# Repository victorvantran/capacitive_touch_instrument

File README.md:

# capacitive_touch_instrument
Capacitive touch instrument built with AT42QT1110 daisy-chained

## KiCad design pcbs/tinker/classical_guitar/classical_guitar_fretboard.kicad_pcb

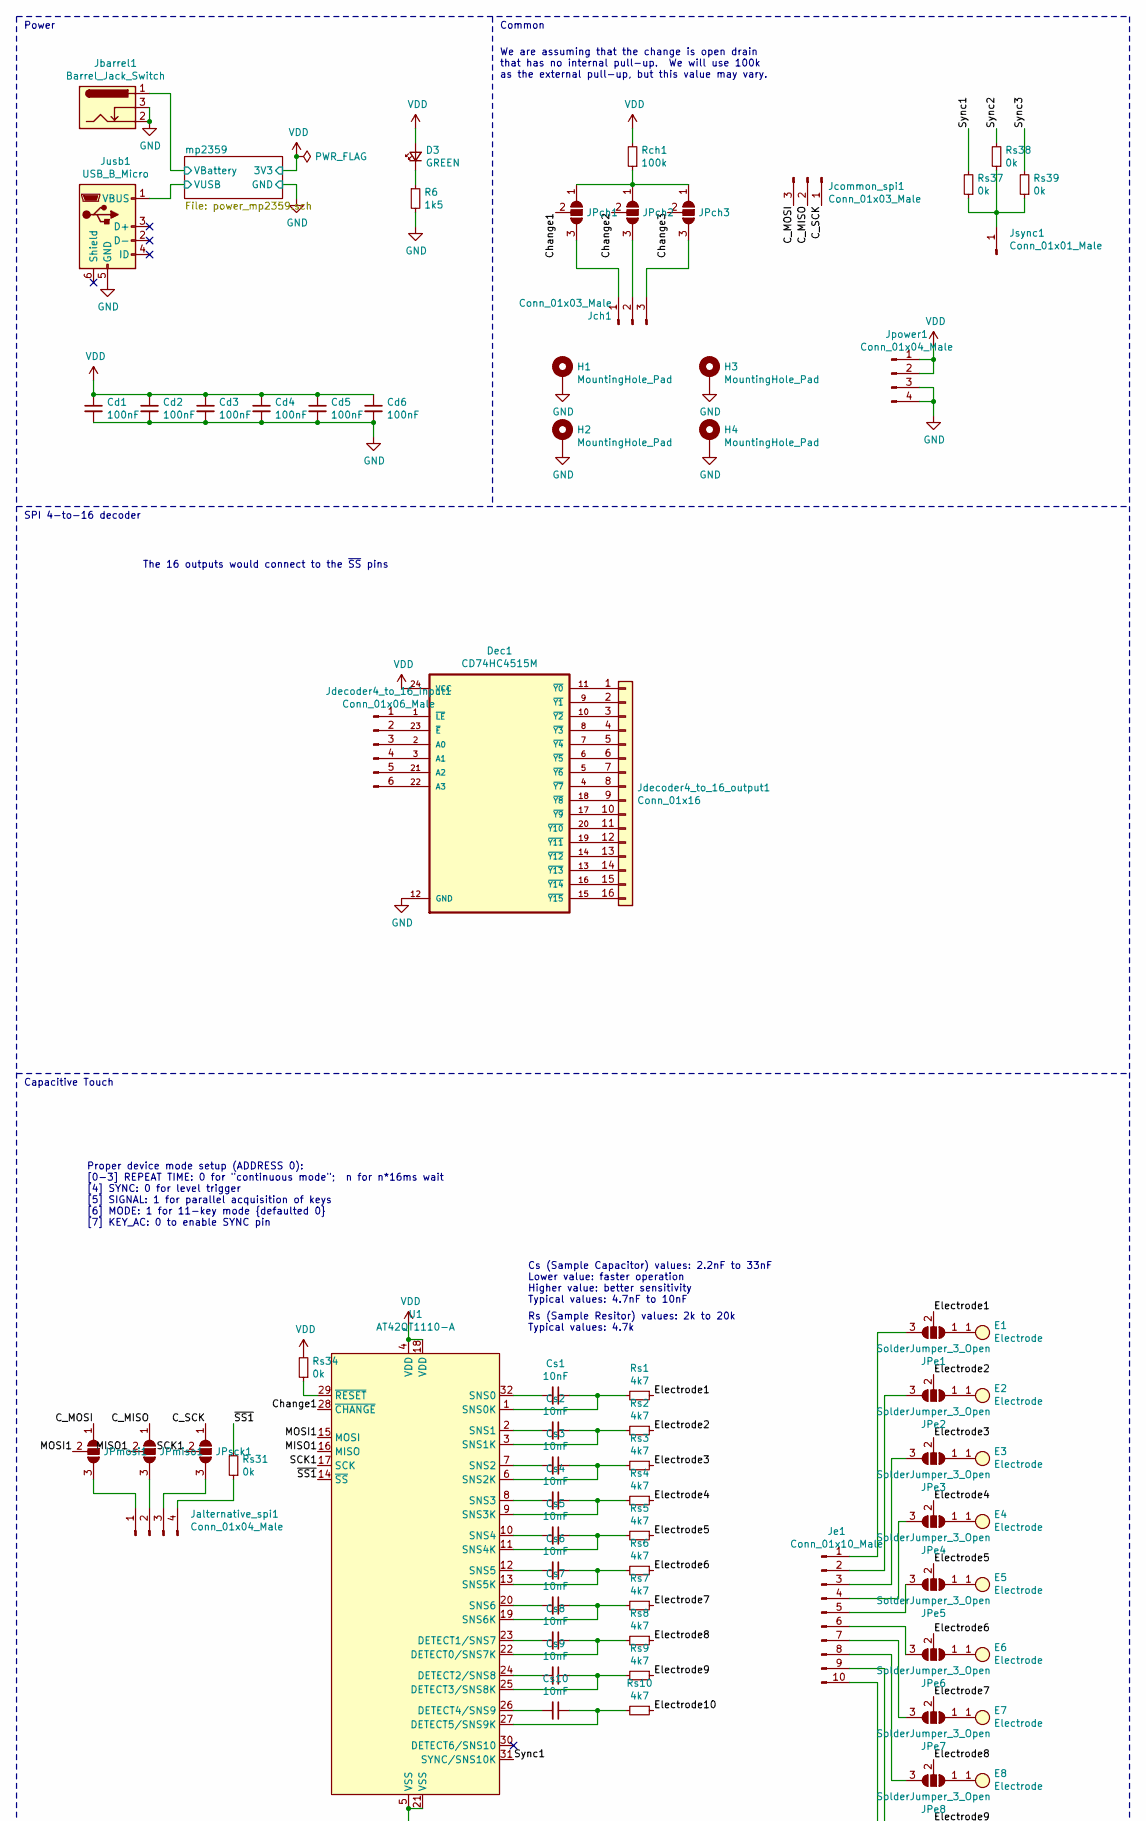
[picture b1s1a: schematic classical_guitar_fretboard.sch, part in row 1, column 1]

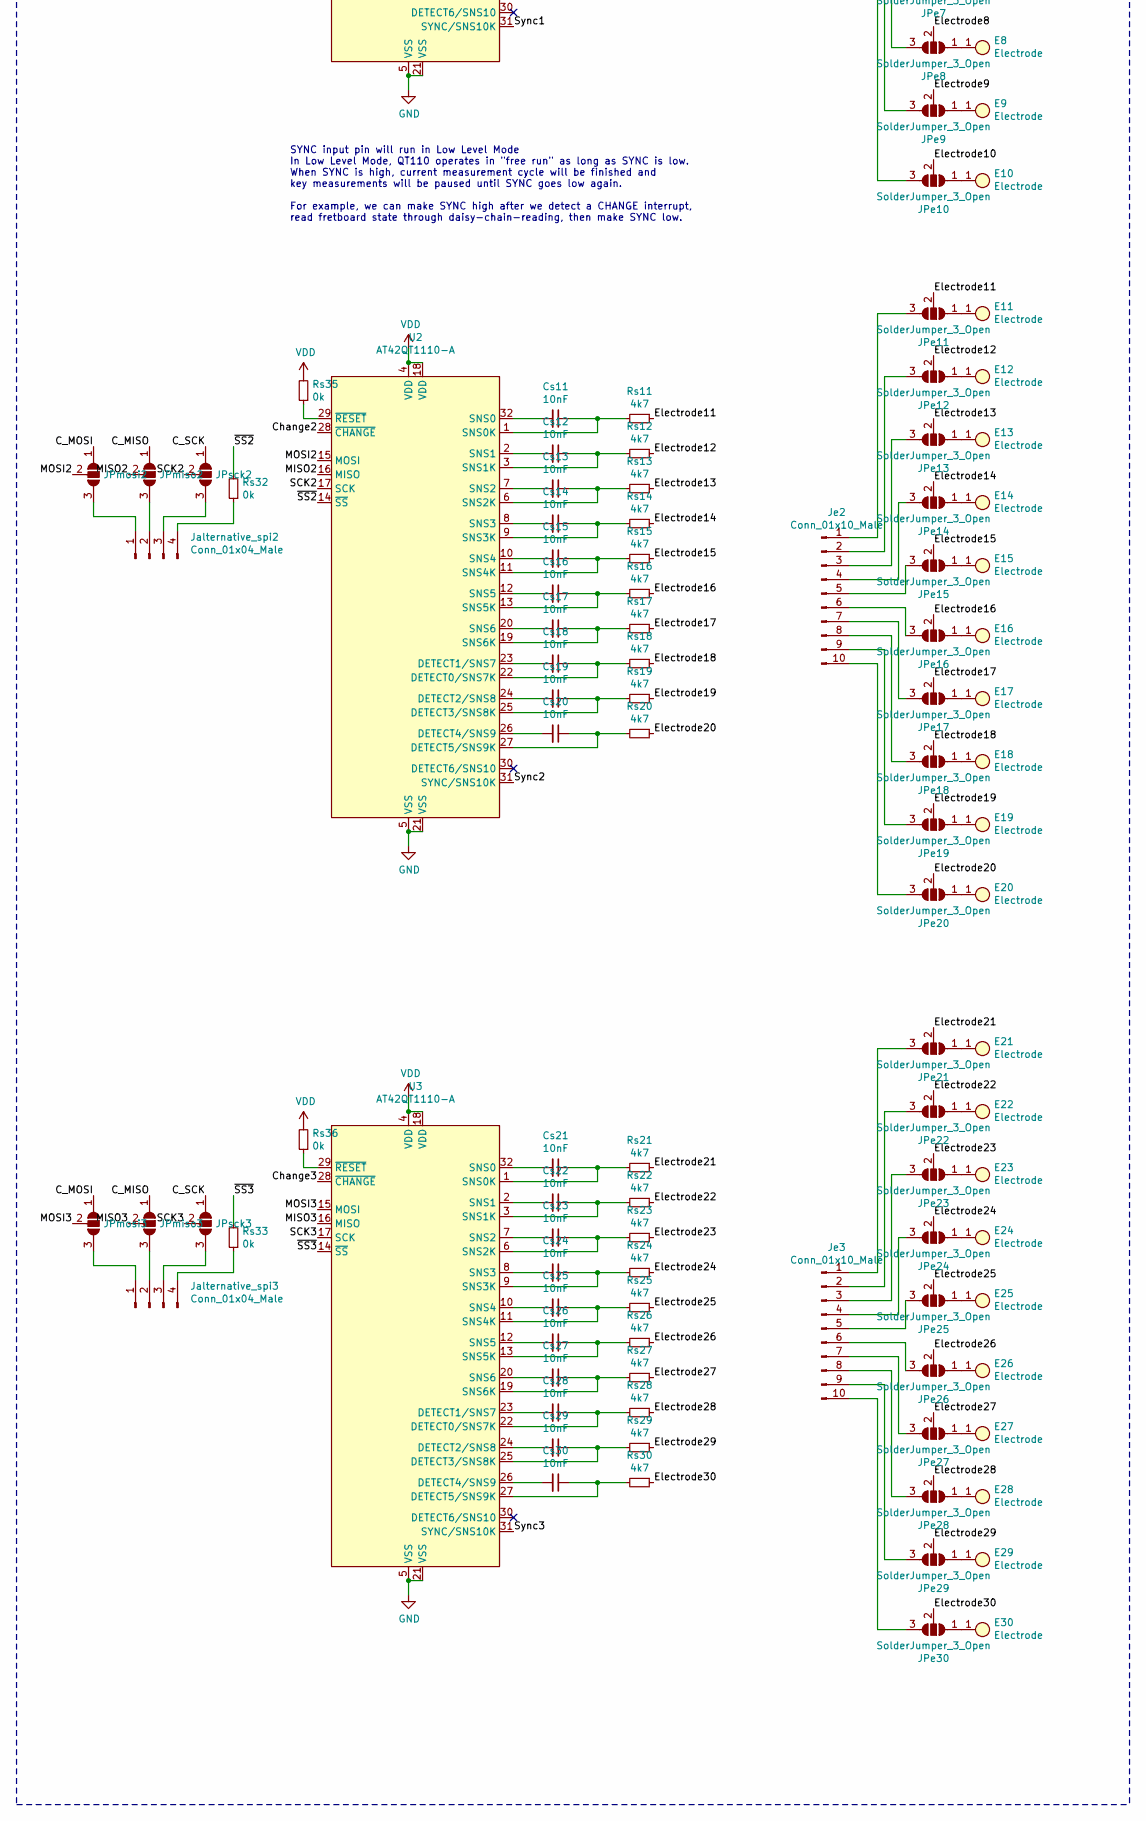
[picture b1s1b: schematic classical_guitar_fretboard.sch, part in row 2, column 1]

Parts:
Cd1, Cd2, Cd3, Cd4, Cd5, Cd6: 100nF; C_0402_1005Metric_Pad0.74x0.62mm_HandSolder
Cs1, Cs2, Cs3, Cs4, Cs5, Cs6, Cs7, Cs8, Cs9, Cs10, Cs11, Cs12, Cs13, Cs14, Cs15, Cs16, Cs17, Cs18, Cs19, Cs20, Cs21, Cs22, Cs23, Cs24, Cs25, Cs26, Cs27, Cs28, Cs29, Cs30: 10nF; C_0603_1608Metric_Pad1.08x0.95mm_HandSolder
D3: GREEN; LED_0603_1608Metric; LCSC Part # C2286
Dec1: CD74HC4515M; SOIC-24W_7.5x15.4mm_P1.27mm
E1, E2, E3, E4, E5, E6, E7, E8, E9, E10, E11, E12, E13, E14, E15, E16, E17, E18, E19, E20, E21, E22, E23, E24, E25, E26, E27, E28, E29, E30: Electrode; Circle_10mm
H1, H2, H3, H4: MountingHole_Pad; MountingHole_4.3mm_M4_Pad_Via
JPch1, JPch2, JPch3: SolderJumper_3_Open; SolderJumper-3_P1.3mm_Open_RoundedPad1.0x1.5mm_NumberLabels
JPe1, JPe2, JPe3, JPe4, JPe5, JPe6, JPe7, JPe8, JPe9, JPe10, JPe11, JPe12, JPe13, JPe14, JPe15, JPe16, JPe17, JPe18, JPe19, JPe20, JPe21, JPe22, JPe23, JPe24, JPe25, JPe26, JPe27, JPe28, JPe29, JPe30: SolderJumper_3_Open; SolderJumper-3_P1.3mm_Open_RoundedPad1.0x1.5mm_NumberLabels
JPmiso1, JPmiso2, JPmiso3: SolderJumper_3_Open; SolderJumper-3_P1.3mm_Open_RoundedPad1.0x1.5mm_NumberLabels
JPmosi1, JPmosi2, JPmosi3: SolderJumper_3_Open; SolderJumper-3_P1.3mm_Open_RoundedPad1.0x1.5mm_NumberLabels
JPsck1, JPsck2, JPsck3: SolderJumper_3_Open; SolderJumper-3_P1.3mm_Open_RoundedPad1.0x1.5mm_NumberLabels
Jalternative_spi1, Jalternative_spi2, Jalternative_spi3: Conn_01x04_Male; PinSocket_1x04_P2.54mm_Vertical
Jbarrel1: Barrel_Jack_Switch; BarrelJack_Horizontal
Jch1: Conn_01x03_Male; PinSocket_1x03_P2.54mm_Vertical
Jcommon_spi1: Conn_01x03_Male; PinSocket_1x03_P2.54mm_Vertical
Jdecoder4_to_16_input1: Conn_01x06_Male; PinHeader_1x06_P2.54mm_Vertical
Jdecoder4_to_16_output1: Conn_01x16; PinSocket_1x16_P2.54mm_Vertical
Je1, Je2, Je3: Conn_01x10_Male; PinSocket_1x10_P2.54mm_Vertical
Jpower1: Conn_01x04_Male; PinSocket_1x04_P2.54mm_Vertical
Jsync1: Conn_01x01_Male; PinSocket_1x01_P2.54mm_Vertical
Jusb1: USB_B_Micro; USB_Micro-B_Amphenol_10118194_Horizontal
R6: 1k5; R_0603_1608Metric; LCSC Part # C22843
Rch1: 100k; R_0603_1608Metric_Pad0.98x0.95mm_HandSolder
Rs1, Rs2, Rs3, Rs4, Rs5, Rs6, Rs7, Rs8, Rs9, Rs10, Rs11, Rs12, Rs13, Rs14, Rs15, Rs16, Rs17, Rs18, Rs19, Rs20, Rs21, Rs22, Rs23, Rs24, Rs25, Rs26, Rs27, Rs28, Rs29, Rs30: 4k7; R_0603_1608Metric_Pad0.98x0.95mm_HandSolder
Rs31, Rs32, Rs33, Rs34, Rs35, Rs36, Rs37, Rs38, Rs39: 0k; R_0603_1608Metric_Pad0.98x0.95mm_HandSolder
U1, U2, U3: AT42QT1110-A; TQFP-32_7x7mm_P0.8mm

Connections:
/C_MISO: JPmiso1.1 (A), JPmiso2.1 (A), JPmiso3.1 (A), Jcommon_spi1.2
/C_MOSI: JPmosi1.1 (A), JPmosi2.1 (A), JPmosi3.1 (A), Jcommon_spi1.3
/C_SCK: JPsck1.1 (A), JPsck2.1 (A), JPsck3.1 (A), Jcommon_spi1.1
/Change1: JPch1.2 (C), U1.28 (~CHANGE)
/Change2: JPch2.2 (C), U2.28 (~CHANGE)
/Change3: JPch3.2 (C), U3.28 (~CHANGE)
/Electrode1: JPe1.2 (C), Rs1.1
/Electrode2: JPe2.2 (C), Rs2.1
/Electrode3: JPe3.2 (C), Rs3.1
/Electrode4: JPe4.2 (C), Rs4.1
/Electrode5: JPe5.2 (C), Rs5.1
/Electrode6: JPe6.2 (C), Rs6.1
/Electrode7: JPe7.2 (C), Rs7.1
/Electrode8: JPe8.2 (C), Rs8.1
/Electrode9: JPe9.2 (C), Rs9.1
/Electrode10: JPe10.2 (C), Rs10.1
/Electrode11: JPe11.2 (C), Rs11.1
/Electrode12: JPe12.2 (C), Rs12.1
/Electrode13: JPe13.2 (C), Rs13.1
/Electrode14: JPe14.2 (C), Rs14.1
/Electrode15: JPe15.2 (C), Rs15.1
/Electrode16: JPe16.2 (C), Rs16.1
/Electrode17: JPe17.2 (C), Rs17.1
/Electrode18: JPe18.2 (C), Rs18.1
/Electrode19: JPe19.2 (C), Rs19.1
/Electrode20: JPe20.2 (C), Rs20.1
/Electrode21: JPe21.2 (C), Rs21.1
/Electrode22: JPe22.2 (C), Rs22.1
/Electrode23: JPe23.2 (C), Rs23.1
/Electrode24: JPe24.2 (C), Rs24.1
/Electrode25: JPe25.2 (C), Rs25.1
/Electrode26: JPe26.2 (C), Rs26.1
/Electrode27: JPe27.2 (C), Rs27.1
/Electrode28: JPe28.2 (C), Rs28.1
/Electrode29: JPe29.2 (C), Rs29.1
/Electrode30: JPe30.2 (C), Rs30.1
/MISO1: JPmiso1.2 (C), U1.16 (MISO)
/MISO2: JPmiso2.2 (C), U2.16 (MISO)
/MISO3: JPmiso3.2 (C), U3.16 (MISO)
/MOSI1: JPmosi1.2 (C), U1.15 (MOSI)
/MOSI2: JPmosi2.2 (C), U2.15 (MOSI)
/MOSI3: JPmosi3.2 (C), U3.15 (MOSI)
/SCK1: JPsck1.2 (C), U1.17 (SCK)
/SCK2: JPsck2.2 (C), U2.17 (SCK)
/SCK3: JPsck3.2 (C), U3.17 (SCK)
/Sync1: Rs37.2, U1.31 (SYNC/SNS10K)
/Sync2: Rs38.2, U2.31 (SYNC/SNS10K)
/Sync3: Rs39.2, U3.31 (SYNC/SNS10K)
/mp2359/VBattery: Jbarrel1.1; also elsewhere on the board
/mp2359/VUSB: Jusb1.1 (VBUS); also elsewhere on the board
/~SS1: Rs31.2, U1.14 (~SS)
/~SS2: Rs32.2, U2.14 (~SS)
/~SS3: Rs33.2, U3.14 (~SS)
GND: Cd1.2, Cd2.2, Cd3.2, Cd4.2, Cd5.2, Cd6.2, Dec1.12 (GND), H1.1, H2.1, H3.1, H4.1, Jbarrel1.2, Jbarrel1.3, Jpower1.3, Jpower1.4, Jusb1.5 (GND), R6.2, U1.5 (VSS), U1.21 (VSS), U2.5 (VSS), U2.21 (VSS), U3.5 (VSS), U3.21 (VSS); also elsewhere on the board
unnamed: Cs1.1, Rs1.2, U1.1 (SNS0K)
unnamed: Cs1.2, U1.32 (SNS0)
unnamed: Cs2.1, Rs2.2, U1.3 (SNS1K)
unnamed: Cs2.2, U1.2 (SNS1)
unnamed: Cs3.1, Rs3.2, U1.6 (SNS2K)
unnamed: Cs3.2, U1.7 (SNS2)
unnamed: Cs4.1, Rs4.2, U1.9 (SNS3K)
unnamed: Cs4.2, U1.8 (SNS3)
unnamed: Cs5.1, Rs5.2, U1.11 (SNS4K)
unnamed: Cs5.2, U1.10 (SNS4)
unnamed: Cs6.1, Rs6.2, U1.13 (SNS5K)
unnamed: Cs6.2, U1.12 (SNS5)
unnamed: Cs7.1, Rs7.2, U1.19 (SNS6K)
unnamed: Cs7.2, U1.20 (SNS6)
unnamed: Cs8.1, Rs8.2, U1.22 (DETECT0/SNS7K)
unnamed: Cs8.2, U1.23 (DETECT1/SNS7)
unnamed: Cs9.1, Rs9.2, U1.25 (DETECT3/SNS8K)
unnamed: Cs9.2, U1.24 (DETECT2/SNS8)
unnamed: Cs10.1, Rs10.2, U1.27 (DETECT5/SNS9K)
unnamed: Cs10.2, U1.26 (DETECT4/SNS9)
unnamed: Cs11.1, Rs11.2, U2.1 (SNS0K)
unnamed: Cs11.2, U2.32 (SNS0)
unnamed: Cs12.1, Rs12.2, U2.3 (SNS1K)
unnamed: Cs12.2, U2.2 (SNS1)
unnamed: Cs13.1, Rs13.2, U2.6 (SNS2K)
unnamed: Cs13.2, U2.7 (SNS2)
unnamed: Cs14.1, Rs14.2, U2.9 (SNS3K)
unnamed: Cs14.2, U2.8 (SNS3)
unnamed: Cs15.1, Rs15.2, U2.11 (SNS4K)
unnamed: Cs15.2, U2.10 (SNS4)
unnamed: Cs16.1, Rs16.2, U2.13 (SNS5K)
unnamed: Cs16.2, U2.12 (SNS5)
unnamed: Cs17.1, Rs17.2, U2.19 (SNS6K)
unnamed: Cs17.2, U2.20 (SNS6)
unnamed: Cs18.1, Rs18.2, U2.22 (DETECT0/SNS7K)
unnamed: Cs18.2, U2.23 (DETECT1/SNS7)
unnamed: Cs19.1, Rs19.2, U2.25 (DETECT3/SNS8K)
unnamed: Cs19.2, U2.24 (DETECT2/SNS8)
unnamed: Cs20.1, Rs20.2, U2.27 (DETECT5/SNS9K)
unnamed: Cs20.2, U2.26 (DETECT4/SNS9)
unnamed: Cs21.1, Rs21.2, U3.1 (SNS0K)
unnamed: Cs21.2, U3.32 (SNS0)
unnamed: Cs22.1, Rs22.2, U3.3 (SNS1K)
unnamed: Cs22.2, U3.2 (SNS1)
unnamed: Cs23.1, Rs23.2, U3.6 (SNS2K)
unnamed: Cs23.2, U3.7 (SNS2)
unnamed: Cs24.1, Rs24.2, U3.9 (SNS3K)
unnamed: Cs24.2, U3.8 (SNS3)
unnamed: Cs25.1, Rs25.2, U3.11 (SNS4K)
unnamed: Cs25.2, U3.10 (SNS4)
unnamed: Cs26.1, Rs26.2, U3.13 (SNS5K)
unnamed: Cs26.2, U3.12 (SNS5)
unnamed: Cs27.1, Rs27.2, U3.19 (SNS6K)
unnamed: Cs27.2, U3.20 (SNS6)
unnamed: Cs28.1, Rs28.2, U3.22 (DETECT0/SNS7K)
unnamed: Cs28.2, U3.23 (DETECT1/SNS7)
unnamed: Cs29.1, Rs29.2, U3.25 (DETECT3/SNS8K)
unnamed: Cs29.2, U3.24 (DETECT2/SNS8)
unnamed: Cs30.1, Rs30.2, U3.27 (DETECT5/SNS9K)
unnamed: Cs30.2, U3.26 (DETECT4/SNS9)
unnamed: D3.1 (K), R6.1
unnamed: Dec1.1 (~LE), Jdecoder4_to_16_input1.1
unnamed: Dec1.2 (A0), Jdecoder4_to_16_input1.3
unnamed: Dec1.3 (A1), Jdecoder4_to_16_input1.4
unnamed: Dec1.4 (~Y7), Jdecoder4_to_16_output1.8
unnamed: Dec1.5 (~Y6), Jdecoder4_to_16_output1.7
unnamed: Dec1.6 (~Y5), Jdecoder4_to_16_output1.6
unnamed: Dec1.7 (~Y4), Jdecoder4_to_16_output1.5
unnamed: Dec1.8 (~Y3), Jdecoder4_to_16_output1.4
unnamed: Dec1.9 (~Y1), Jdecoder4_to_16_output1.2
unnamed: Dec1.10 (~Y2), Jdecoder4_to_16_output1.3
unnamed: Dec1.11 (~Y0), Jdecoder4_to_16_output1.1
unnamed: Dec1.13 (~Y13), Jdecoder4_to_16_output1.14
unnamed: Dec1.14 (~Y12), Jdecoder4_to_16_output1.13
unnamed: Dec1.15 (~Y15), Jdecoder4_to_16_output1.16
unnamed: Dec1.16 (~Y14), Jdecoder4_to_16_output1.15
unnamed: Dec1.17 (~Y9), Jdecoder4_to_16_output1.10
unnamed: Dec1.18 (~Y8), Jdecoder4_to_16_output1.9
unnamed: Dec1.19 (~Y11), Jdecoder4_to_16_output1.12
unnamed: Dec1.20 (~Y10), Jdecoder4_to_16_output1.11
unnamed: Dec1.21 (A2), Jdecoder4_to_16_input1.5
unnamed: Dec1.22 (A3), Jdecoder4_to_16_input1.6
unnamed: Dec1.23 (~E), Jdecoder4_to_16_input1.2
unnamed: E1.1, JPe1.1 (A)
unnamed: E2.1, JPe2.1 (A)
unnamed: E3.1, JPe3.1 (A)
unnamed: E4.1, JPe4.1 (A)
unnamed: E5.1, JPe5.1 (A)
unnamed: E6.1, JPe6.1 (A)
unnamed: E7.1, JPe7.1 (A)
unnamed: E8.1, JPe8.1 (A)
unnamed: E9.1, JPe9.1 (A)
unnamed: E10.1, JPe10.1 (A)
unnamed: E11.1, JPe11.1 (A)
unnamed: E12.1, JPe12.1 (A)
unnamed: E13.1, JPe13.1 (A)
unnamed: E14.1, JPe14.1 (A)
unnamed: E15.1, JPe15.1 (A)
unnamed: E16.1, JPe16.1 (A)
unnamed: E17.1, JPe17.1 (A)
unnamed: E18.1, JPe18.1 (A)
unnamed: E19.1, JPe19.1 (A)
unnamed: E20.1, JPe20.1 (A)
unnamed: E21.1, JPe21.1 (A)
unnamed: E22.1, JPe22.1 (A)
unnamed: E23.1, JPe23.1 (A)
unnamed: E24.1, JPe24.1 (A)
unnamed: E25.1, JPe25.1 (A)
unnamed: E26.1, JPe26.1 (A)
unnamed: E27.1, JPe27.1 (A)
unnamed: E28.1, JPe28.1 (A)
unnamed: E29.1, JPe29.1 (A)
unnamed: E30.1, JPe30.1 (A)
unnamed: JPch1.1 (A), JPch2.1 (A), JPch3.1 (A), Rch1.1
unnamed: JPch1.3 (B), Jch1.1
unnamed: JPch2.3 (B), Jch1.2
unnamed: JPch3.3 (B), Jch1.3
unnamed: JPe1.3 (B), Je1.1
unnamed: JPe2.3 (B), Je1.2
unnamed: JPe3.3 (B), Je1.3
unnamed: JPe4.3 (B), Je1.4
unnamed: JPe5.3 (B), Je1.5
unnamed: JPe6.3 (B), Je1.6
unnamed: JPe7.3 (B), Je1.7
unnamed: JPe8.3 (B), Je1.8
unnamed: JPe9.3 (B), Je1.9
unnamed: JPe10.3 (B), Je1.10
unnamed: JPe11.3 (B), Je2.1
unnamed: JPe12.3 (B), Je2.2
unnamed: JPe13.3 (B), Je2.3
unnamed: JPe14.3 (B), Je2.4
unnamed: JPe15.3 (B), Je2.5
unnamed: JPe16.3 (B), Je2.6
unnamed: JPe17.3 (B), Je2.7
unnamed: JPe18.3 (B), Je2.8
unnamed: JPe19.3 (B), Je2.9
unnamed: JPe20.3 (B), Je2.10
unnamed: JPe21.3 (B), Je3.1
unnamed: JPe22.3 (B), Je3.2
unnamed: JPe23.3 (B), Je3.3
unnamed: JPe24.3 (B), Je3.4
unnamed: JPe25.3 (B), Je3.5
unnamed: JPe26.3 (B), Je3.6
unnamed: JPe27.3 (B), Je3.7
unnamed: JPe28.3 (B), Je3.8
unnamed: JPe29.3 (B), Je3.9
unnamed: JPe30.3 (B), Je3.10
unnamed: JPmiso1.3 (B), Jalternative_spi1.2
unnamed: JPmiso2.3 (B), Jalternative_spi2.2
unnamed: JPmiso3.3 (B), Jalternative_spi3.2
unnamed: JPmosi1.3 (B), Jalternative_spi1.1
unnamed: JPmosi2.3 (B), Jalternative_spi2.1
unnamed: JPmosi3.3 (B), Jalternative_spi3.1
unnamed: JPsck1.3 (B), Jalternative_spi1.3
unnamed: JPsck2.3 (B), Jalternative_spi2.3
unnamed: JPsck3.3 (B), Jalternative_spi3.3
unnamed: Jalternative_spi1.4, Rs31.1
unnamed: Jalternative_spi2.4, Rs32.1
unnamed: Jalternative_spi3.4, Rs33.1
unnamed: Jsync1.1, Rs37.1, Rs38.1, Rs39.1
unnamed: Rs34.1, U1.29 (~RESET)
unnamed: Rs35.1, U2.29 (~RESET)
unnamed: Rs36.1, U3.29 (~RESET)
VDD: Cd1.1, Cd2.1, Cd3.1, Cd4.1, Cd5.1, Cd6.1, D3.2 (A), Dec1.24 (VCC), Jpower1.1, Jpower1.2, Rch1.2, Rs34.2, Rs35.2, Rs36.2, U1.4 (VDD), U1.18 (VDD), U2.4 (VDD), U2.18 (VDD), U3.4 (VDD), U3.18 (VDD); also elsewhere on the board

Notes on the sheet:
Power
Common
Capacitive Touch
The 16 outputs would connect to the ~SS~ pins
We are assuming that the change is open drain that has no internal pull-up. We will use 100k as the external pull-up, but this value may vary.
Proper device mode setup (ADDRESS 0): [0-3] REPEAT TIME: 0 for "continuous mode"; n for n*16ms wait [4] SYNC: 0 for level trigger [5] SIGNAL: 1 for parallel acquisition of keys [6] MODE: 1 for 11-key mode {defaulted 0} [7] KEY_AC: 0 to enable SYNC pin
Rs (Sample Resitor) values: 2k to 20k Typical values: 4.7k
Cs (Sample Capacitor) values: 2.2nF to 33nF Lower value: faster operation Higher value: better sensitivity Typical values: 4.7nF to 10nF
SYNC input pin will run in Low Level Mode In Low Level Mode, QT110 operates in "free run" as long as SYNC is low. When SYNC is high, current measurement cycle will be finished and key measurements will be paused until SYNC goes low again. For example, we can make SYNC high after we detect a CHANGE 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
SPI 4-to-16 decoder

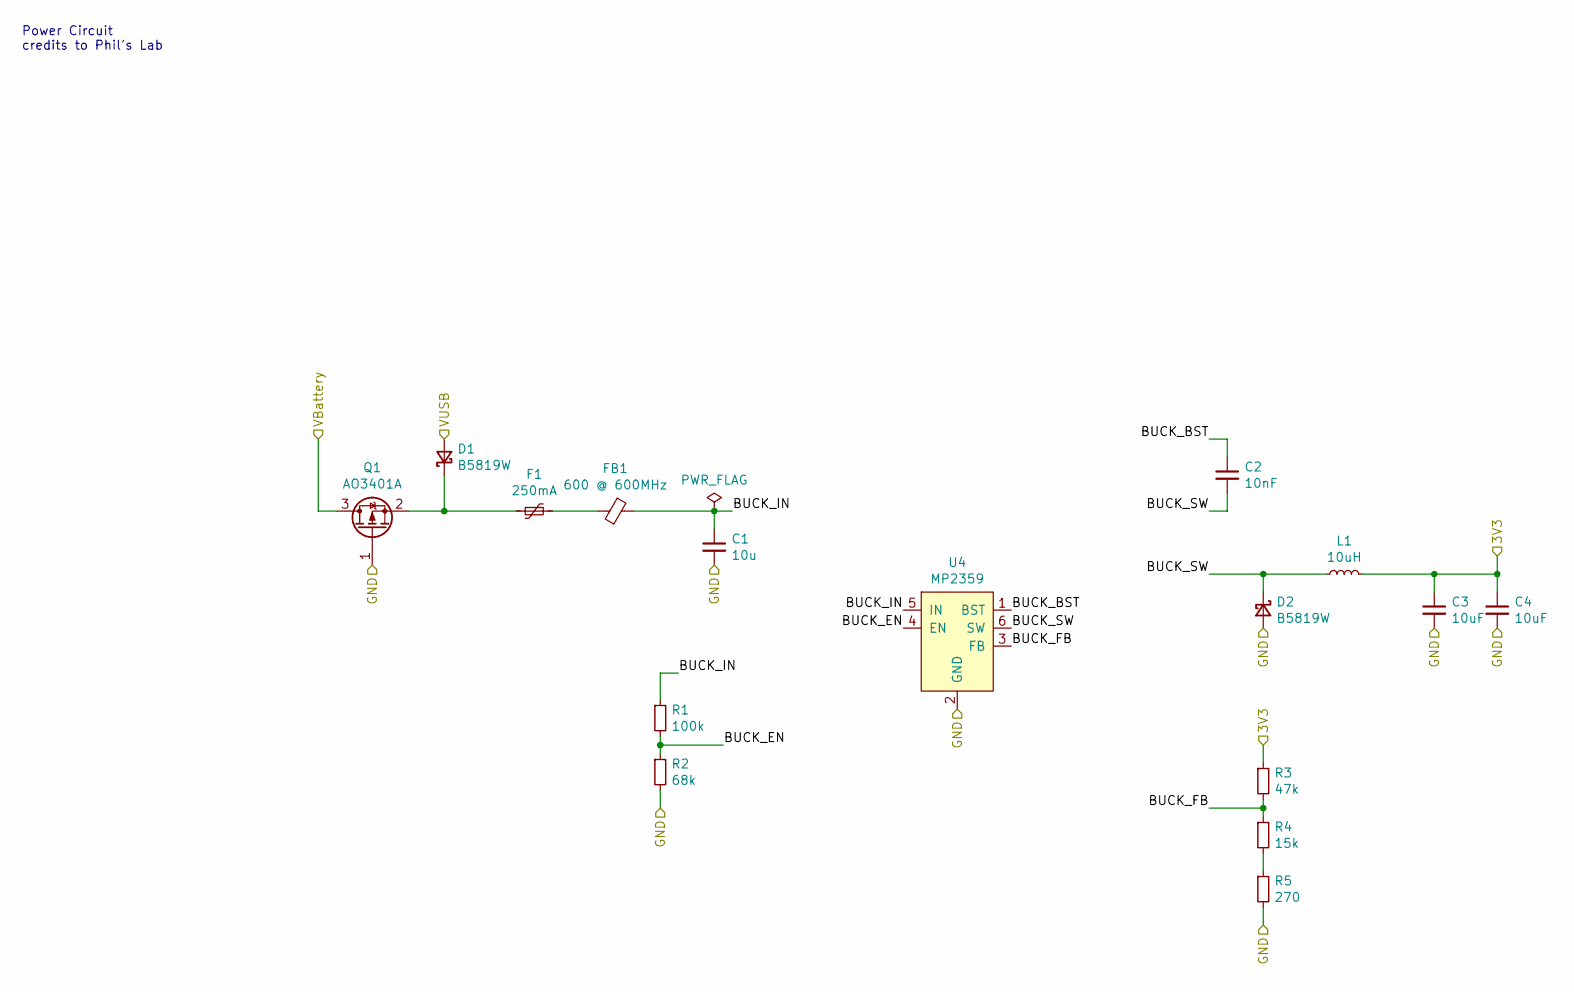
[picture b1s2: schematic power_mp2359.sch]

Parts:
C1: 10u; C_1206_3216Metric_Pad1.33x1.80mm_HandSolder; LCSC Part # C13585
C2: 10nF; C_0603_1608Metric_Pad1.08x0.95mm_HandSolder; LCSC Part # C57112
C3, C4: 10uF; C_1206_3216Metric_Pad1.33x1.80mm_HandSolder; LCSC Part # C13585
D1, D2: B5819W; D_SOD-123; LCSC Part # C8598
F1: 250mA; Fuse_1206_3216Metric; LCSC Part # C369159
FB1: 600 @ 600MHz; L_0805_2012Metric; LCSC Part # C1017
L1: 10uH; L_Sunlord_MWSA0518_5.4x5.2mm; LCSC Part # C408412
Q1: AO3401A; SOT-23; LCSC Part # C15127
R1: 100k; R_0603_1608Metric; LCSC Part # C25803
R2: 68k; R_0603_1608Metric; LCSC Part # C23231
R3: 47k; R_0603_1608Metric; LCSC Part # C25819
R4: 15k; R_0603_1608Metric; LCSC Part # C22809
R5: 270; R_0603_1608Metric; LCSC Part # C22966
U4: MP2359; SOT-23-6_Handsoldering

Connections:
/mp2359/BUCK_BST: C2.1, U4.1 (BST)
/mp2359/BUCK_EN: R1.2, R2.1, U4.4 (EN)
/mp2359/BUCK_FB: R3.2, R4.1, U4.3 (FB)
/mp2359/BUCK_IN: C1.1, FB1.1, R1.1, U4.5 (IN)
/mp2359/BUCK_SW: C2.2, D2.1 (K), L1.1, U4.6 (SW)
/mp2359/VBattery: Q1.3 (D); also elsewhere on the board
/mp2359/VUSB: D1.2 (A); also elsewhere on the board
GND: C1.2, C3.2, C4.2, D2.2 (A), Q1.1 (G), R2.2, R5.2, U4.2 (GND); also elsewhere on the board
unnamed: D1.1 (K), F1.2, Q1.2 (S)
unnamed: F1.1, FB1.2
unnamed: R4.2, R5.1
VDD: C3.1, C4.1, L1.2, R3.1; also elsewhere on the board

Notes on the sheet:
Power Circuit credits to Phil's Lab

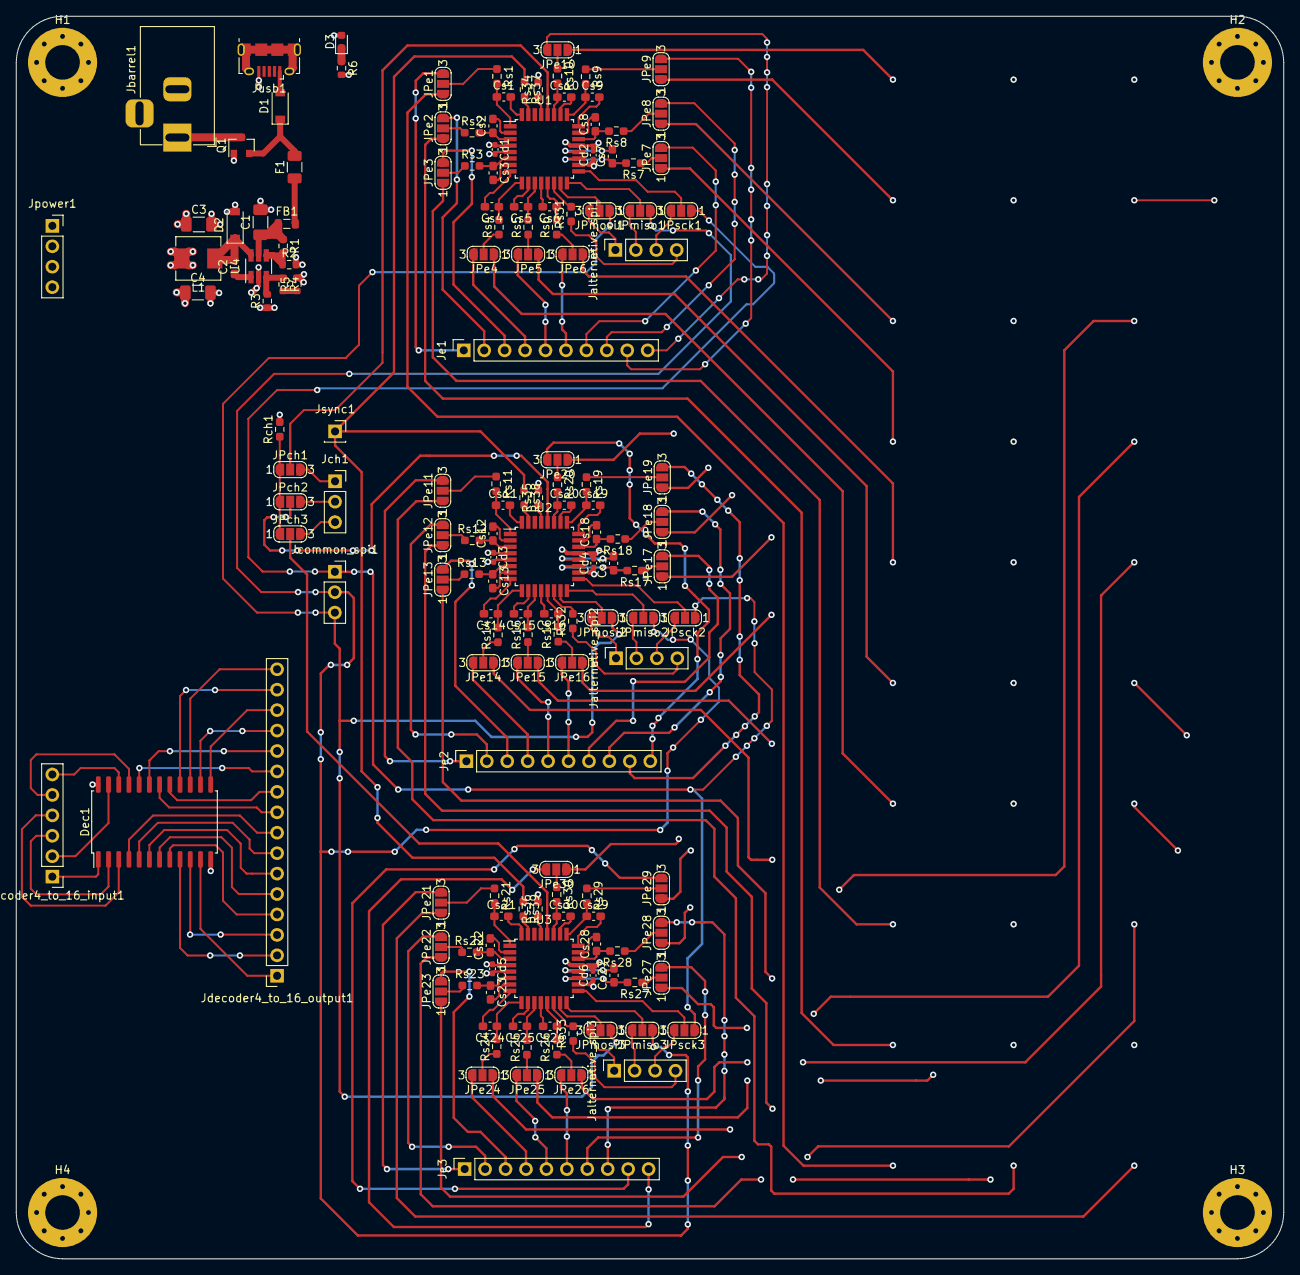
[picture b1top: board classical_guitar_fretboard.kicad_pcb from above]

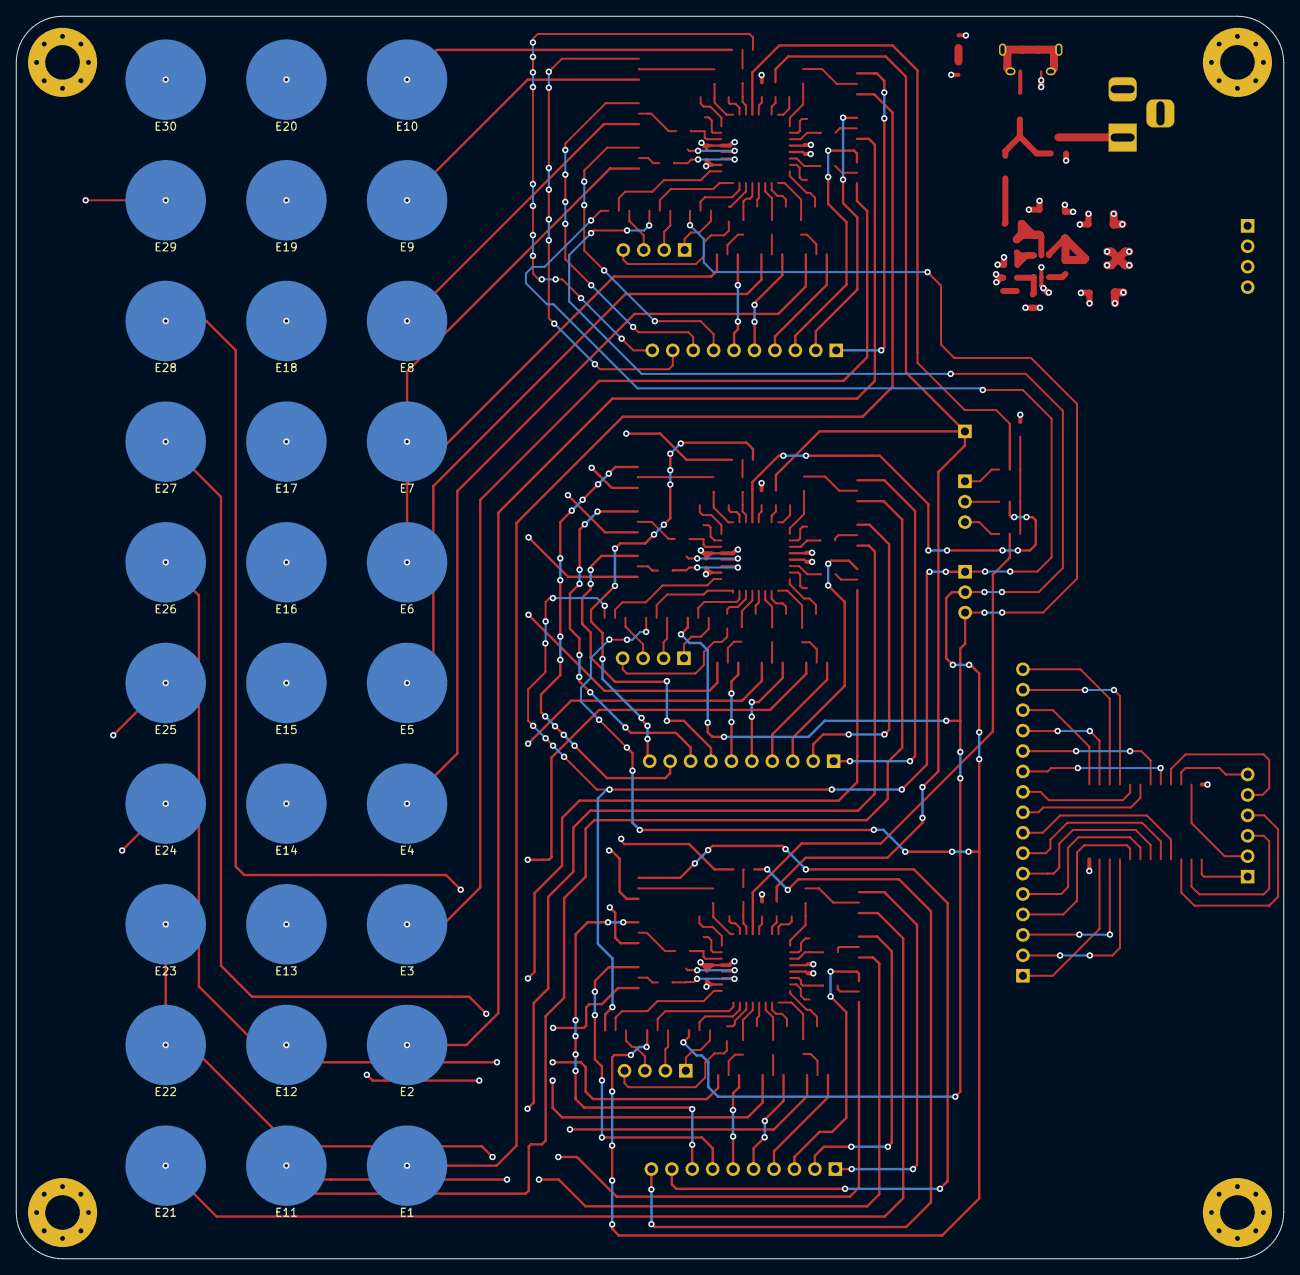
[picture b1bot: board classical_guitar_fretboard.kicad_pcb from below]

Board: 4 copper layers, 157.6 x 154.4 mm, 188 parts (30 on the bottom side), 226 nets.

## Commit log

2021-11-07 Initial pcbs using AT42QT1110
2021-11-07 Rearranged labels
2021-11-07 Rearranged labels 2 and positions
2021-11-07 Added 74HC138 footprint
2021-11-24 Added decoders
2021-11-24 Established 5-to-32 decoder sheet
2021-11-26 Rearranging schematic
2021-11-26 Rearranged schematic again and establishing pcb layout
2021-11-26 Layed out AT32QT1110
2021-11-26 Replaced jumper pads
2021-11-26 Trace for 5-to-32 decoder before replacement with 4-to-16 decoder
2021-11-26 Replaced 5-to-32 decoder with 4-to-16 decoder
2021-11-26 Rearranged jumpers for more efficient wiring
2021-11-26 Completed tracing of second at42qt1110
2021-11-26 Testing electrode tracing
2021-11-26 Testing blind vias
2021-11-27 Replaced CD74HC154ME4 with faster CD74GC4515M with latch
2021-11-30 Prepare electrode tracking
2021-11-30 Adjusted last_move
2021-12-01 Tracing electrodes
2021-12-01 Traced electrodes
2021-12-01 Traced 1st at42qt1110
2021-12-01 Traced 2nd at42qt1110
2021-12-01 Traced 2nd at42qt1110 2
2021-12-17 Almost finalized pcb
2021-12-21 Traces left are VCC and GND
2021-12-21 VDD and GND traces added via vias
2021-12-26 Added rudimentary capacitive touch test
